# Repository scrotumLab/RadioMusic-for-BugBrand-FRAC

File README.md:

# RadioMusic v3.2 for BugBrand Modular System
With the permission of Tom Whitwell (Music Thing Modular), creator of [the original Radio Music module](https://github.com/TomWhitwell/RadioMusic), Scrotum Lab made different versions of the project compatible with the BugBrand Modular System in FRAC format.

This project was only made possible because Tom Whitwell licensed all hardware and software design as Creative Commons: [CC-BY-SA: Attribution / ShareAlike](https://creativecommons.org/licenses/by-sa/3.0/), allowing people to learn and share knowledge.  
Without him or other great creators like Emilie Gillet, I would have been incapable of doing the Scrotum Lab adaptations for the BugBrand system.

Here you will find:
- The latest version of the schematics and board files in Diptrace format.
- The Arduino code which was changed to allow mixing & attenuation to the circuit and works on v3.x versions of the Scrotum Lab module (not the earlier versions which still use the original Music Thing Modular code). 
- The frontpanel design as GERBER file (frontpanels in the BugBrand system are made of PCB material).
- The settings.txt file to put on your SD Card.

As the main purpose of the Scrotum Lab Radio Music was to be used as a sample player, the main markings on the front panel were changed: "Station" became "Sample Select" / "Start" became "Pitch" / "Reset" became "Trig".

Instead of 3.5mm plugs, banana plugs are used like the ones found on the BugBrand system.<br>

2 x CV inputs were added to mix/attenuate the incoming signal at "Sample Select" and "Pitch" inputs.<br> 
These CV inputs now accept bipolar signal -5V/+5V or unipolar +10V.<br> 

Mostly all through hole components were replaced by SMD components (0805).<br>

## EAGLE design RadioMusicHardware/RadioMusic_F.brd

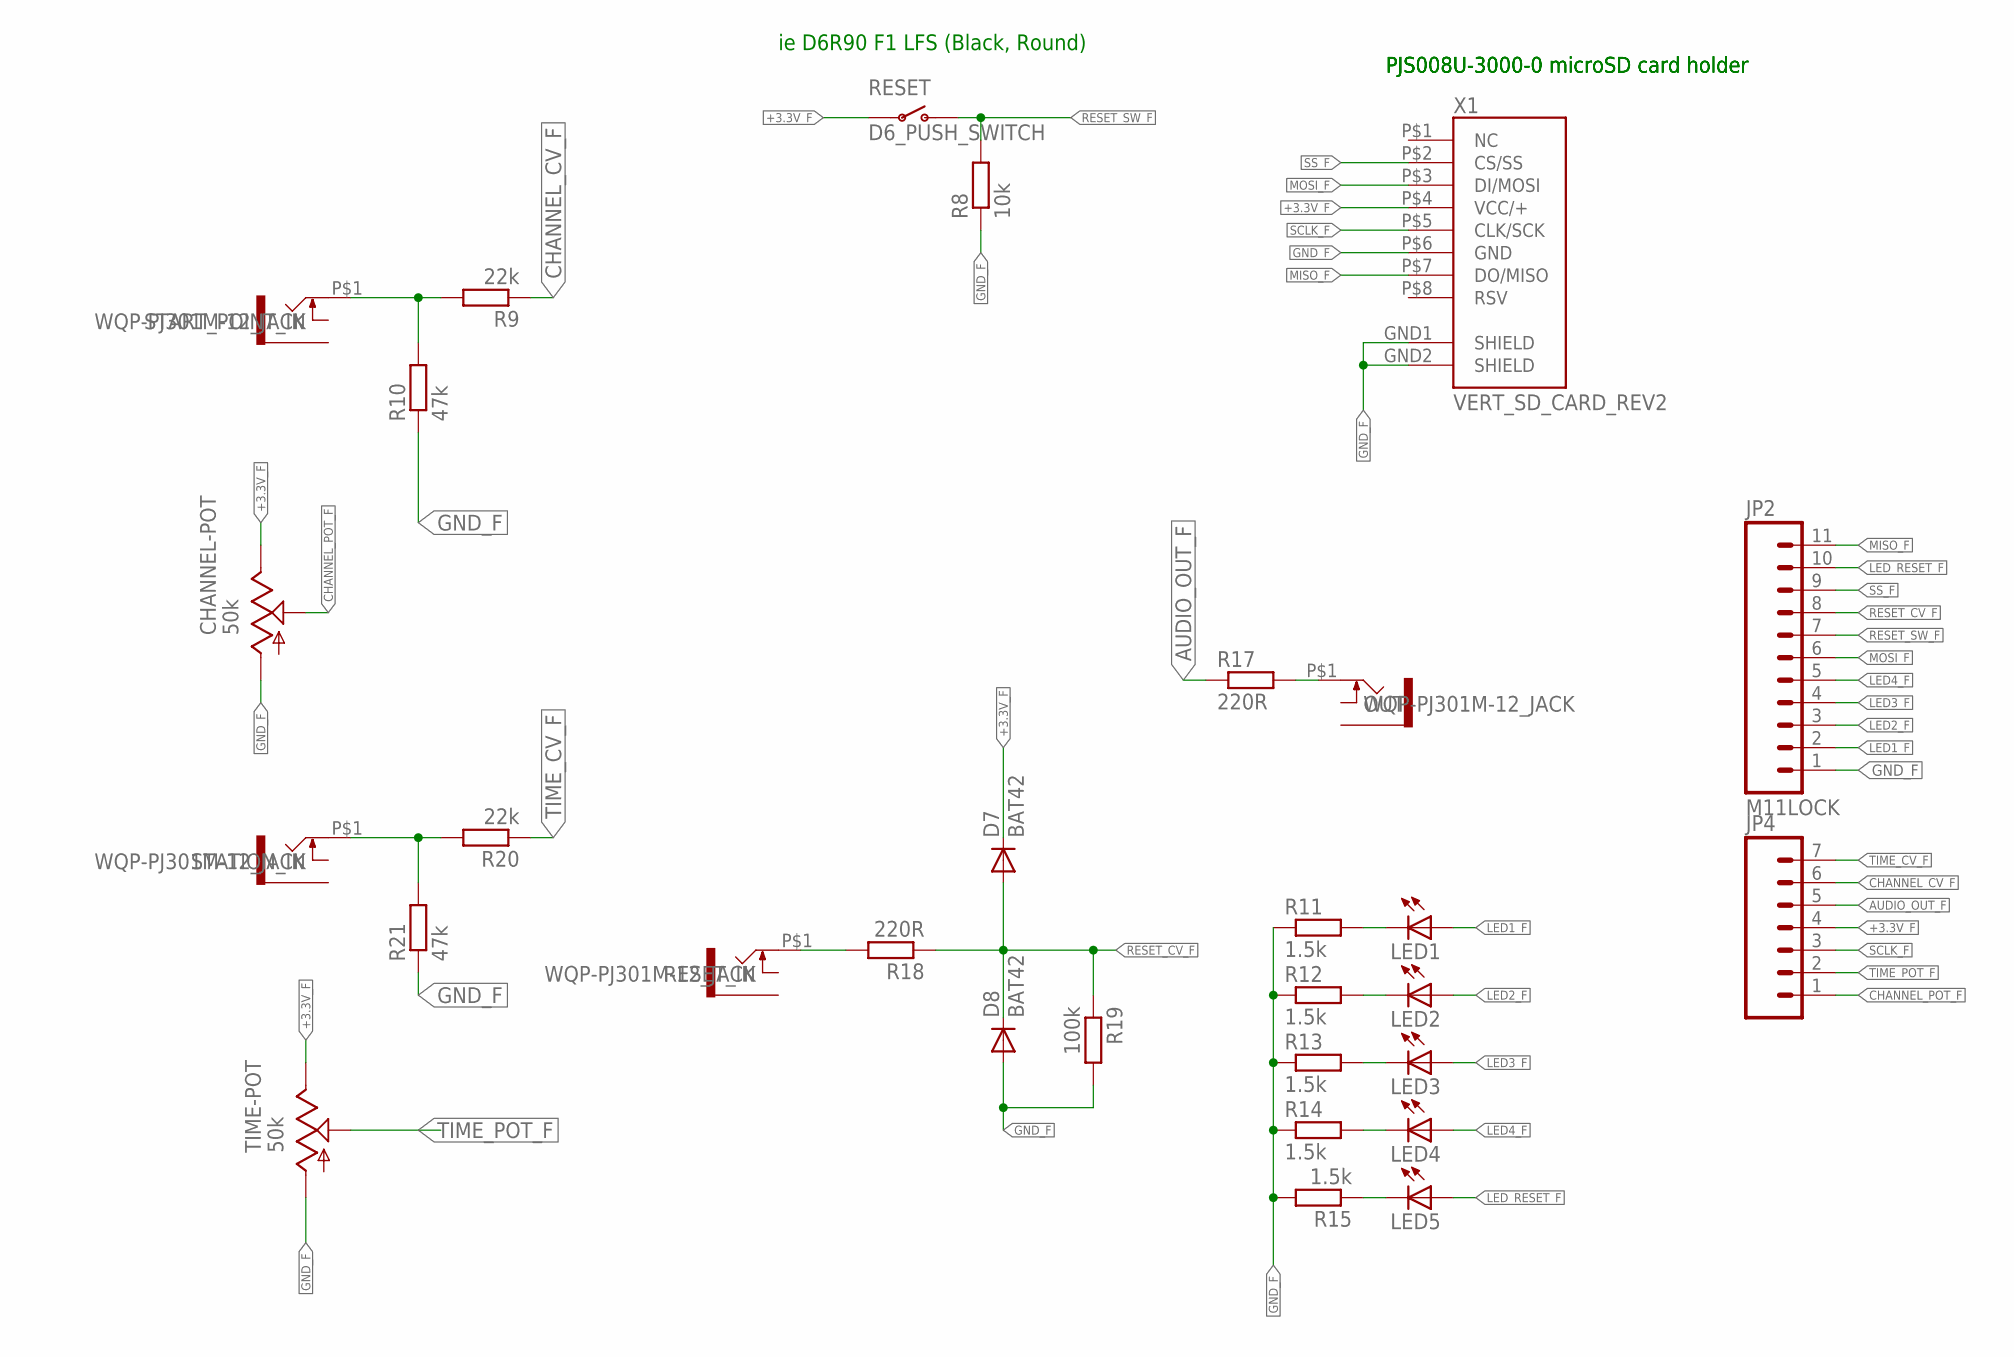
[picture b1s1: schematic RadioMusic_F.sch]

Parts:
CHANNEL-POT: 50k; EVUF
D7, D8: BAT42; DO34-7
JP2: M11LOCK; 1X11_LOCK
JP4: M07LOCK; 1X07_LOCK
LED1, LED2, LED3, LED4, LED5: LED3MM
OUT: WQP-PJ301M-12_JACK
R8: 10k; 0207/10
R9, R20: 22k; 0207/10
R10, R21: 47k; 0207/10
R11, R12, R13, R14, R15: 1.5k; 0207/10
R17, R18: 220R; 0207/10
R19: 100k; 0207/10
RESET: D6_PUSH_SWITCH; D6_BUTTON_RND
RESET_IN: WQP-PJ301M-12_JACK
START_POINT_IN: WQP-PJ301M-12_JACK
STATION_IN: WQP-PJ301M-12_JACK
TIME-POT: 50k; EVUF
X1: VERT_SD_CARD_REV2; VERT_MICROSD_REV2

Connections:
+3.3V_F: CHANNEL-POT.3 (E), D7.C, JP4.4, RESET.P$3, RESET.P$4, TIME-POT.3 (E), X1.P$4 (VCC/+)
AUDIO_OUT_F: JP4.5, R17.1
CHANNEL_CV_F: JP4.6, R9.1
CHANNEL_POT_F: CHANNEL-POT.2 (S), JP4.1
GND_F: CHANNEL-POT.1 (A), D8.A, JP2.1, R8.1, R10.1, R11.1, R12.1, R13.1, R14.1, R15.2, R19.2, R21.1, TIME-POT.1 (A), X1.GND1 (SHIELD), X1.GND2 (SHIELD), X1.P$6 (GND)
LED1_F: JP2.2, LED1.A
LED2_F: JP2.3, LED2.A
LED3_F: JP2.4, LED3.A
LED4_F: JP2.5, LED4.A
LED_RESET_F: JP2.10, LED5.A
MISO_F: JP2.11, X1.P$7 (DO/MISO)
MOSI_F: JP2.6, X1.P$3 (DI/MOSI)
unnamed: OUT.P$1, R17.2
unnamed: R9.2, R10.2, START_POINT_IN.P$1
unnamed: R18.2, RESET_IN.P$1
unnamed: LED1.K (C), R11.2
unnamed: LED2.K (C), R12.2
unnamed: LED3.K (C), R13.2
unnamed: LED4.K (C), R14.2
unnamed: LED5.K (C), R15.1
RESET_CV_F: D7.A, D8.C, JP2.8, R18.1, R19.1
RESET_SW_F: JP2.7, R8.2, RESET.P$1 (O), RESET.P$2 (O)
SCLK_F: JP4.3, X1.P$5 (CLK/SCK)
SS_F: JP2.9, X1.P$2 (CS/SS)
TEMP: R20.2, R21.2, STATION_IN.P$1
TIME_CV_F: JP4.7, R20.1
TIME_POT_F: JP4.2, TIME-POT.2 (S)

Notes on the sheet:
ie D6R90 F1 LFS (Black, Round)
PJS008U-3000-0 microSD card holder

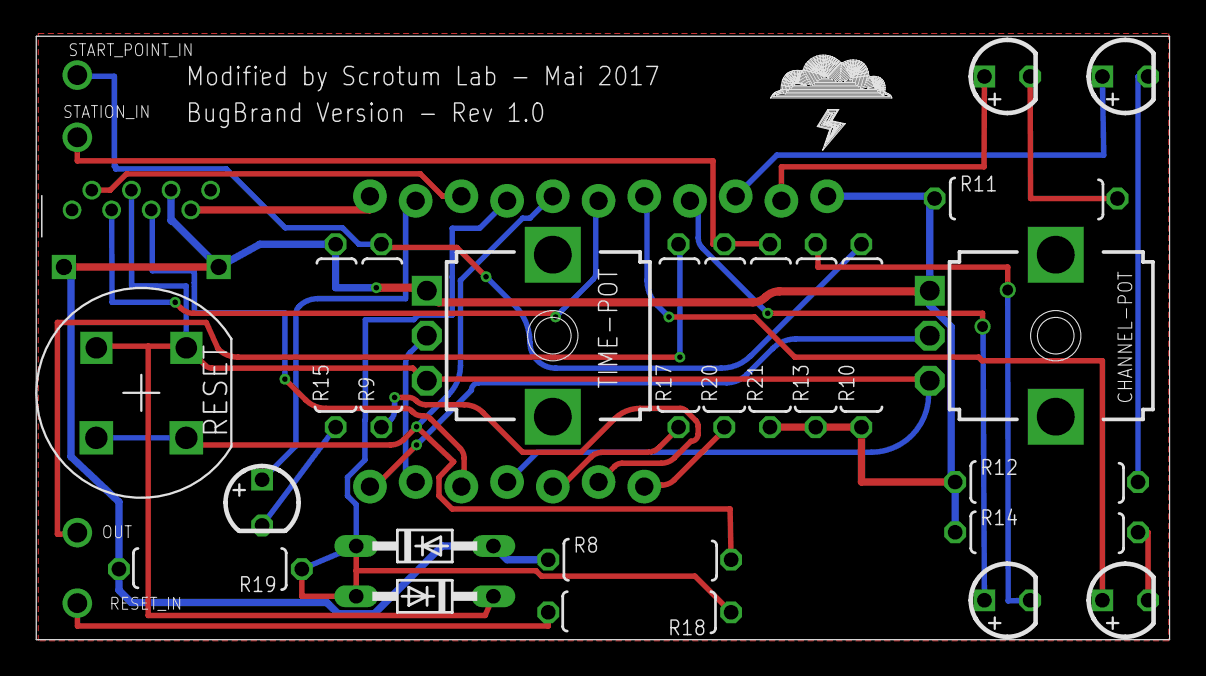
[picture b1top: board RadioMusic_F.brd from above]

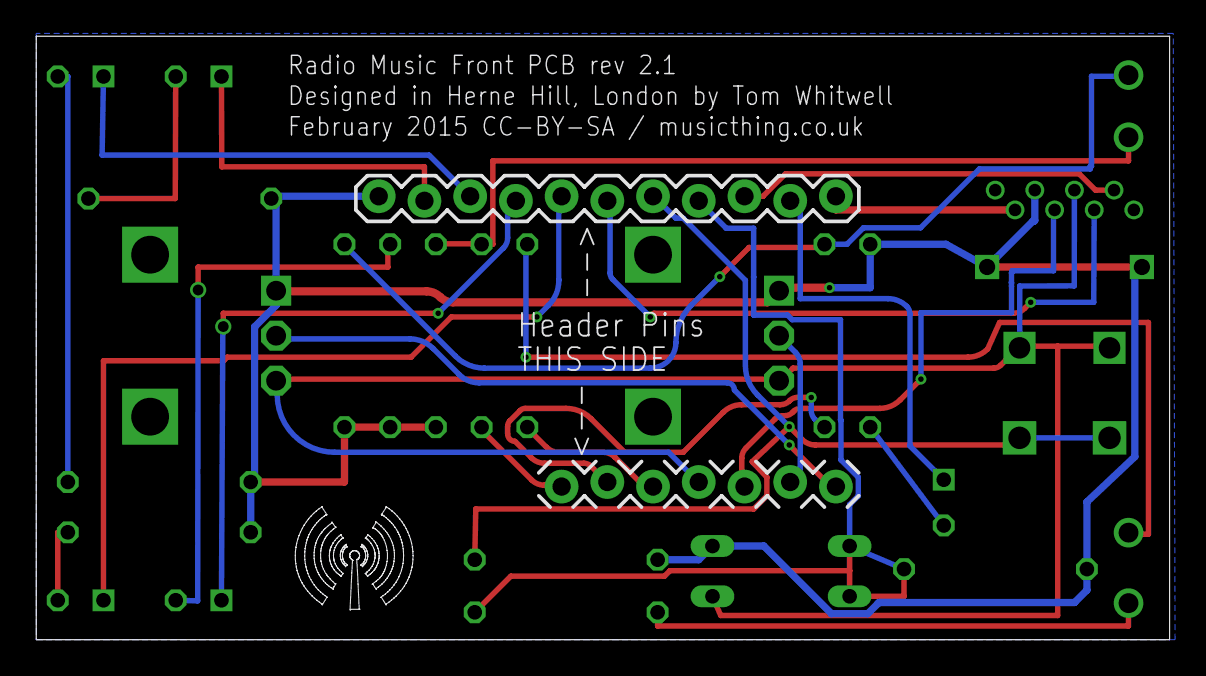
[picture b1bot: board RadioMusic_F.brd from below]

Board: 4 copper layers, 63.0 x 33.5 mm, 30 parts (2 on the bottom side), 27 nets.

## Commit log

2018-05-13 test
    test
2018-05-13 Eagle files
    Rev 1.0
2019-08-22 Uploading Scrotum Lab PCB files
2019-08-22 Deleting original Music Thing PCB files
2023-10-25 Frontpanel
2023-10-25 Chord Organ alt. firmware for v3.1 as .hex file
2023-10-25 Chord Organ alt. firmware for v3.1 .hex in zip
2023-10-25 Telharfauxnium alt. firmware
2023-10-25 Telharfauxnium alt. firmware .hex file in a zip

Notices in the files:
RadioMusicHardware/RadioMusic_F.brd:
February 2015 CC-BY-SA / musicthing.co.uk
parts and their libraries:
SparkFun-Connectors: Licensing: CC v3.0 Share-Alike You are welcome to use this library for commercial purposes.
